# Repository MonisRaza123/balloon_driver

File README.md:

# balloon_driver
LED Balloon Targets is an LED based electronic version of the popular game Shooting Targets. In this game, the player has to shoot at balloon targets using the gun. The LEDs emulate the balloons and a laser gun is used to shoot them. The LED balloons are arranged in a 4 x 3 matrix.
One LED balloon is made of 4 LEDs and an LDR is embedded in the centre. So there is one LDR corresponding to each balloon. The player has to actually aim at the LDR by the laser gun to shoot the LED balloon. All LED balloons are lighted up initially. As soon as laser falls on any LDR, the LEDs of the corresponding balloon turn off. Once all the LED balloons go off, the buzzer is turned on to indicate the same.
Do you have what it takes to be a great shooter? Test your shooting skills using this game. Load the gun, press the trigger and shoot!

Let us first list down the requirements of the proposed project as follows:
- A device to sense the light coming from laser gun.
- An output device to emulate the balloon.
- An output device to indicate that the game is over.
- A microcontroller to do all the processing.
- A supply to power up the whole circuit.

Now we will try to place the above requirements in the six-box model:
1. INPUT: LDR (light-dependent resistor) to detect the change in light when laser falls on it. LDRs are arranged in a 4x3 matrix. 
1. OUTPUTS:
   1. 4 LEDs to emulate one balloon. Bal- loons are also arranged in a 4x3 matrix. 
   2. Buzzer to indicate that the game is complete i.e. all LED balloons have been shot at.
1. MICROCONTROLLER: The microcontroller used is ESP32 Wroom32.
1. POWER SUPPLY: For keeping the project portable, the power is supplied through a USB Mini B connector, which brings in a raw 5V. This voltage is not suitable to be fed directly to the ESP32. Therefore, LM1117 LDO voltage regulator that gives 3.3V output is used.
1. COMMUNICATION: A 4-pin connector, with Test, Reset, Vcc and GND signals, is provided for downloading code from the emulator. This ensures that the user doesn't have to disconnect the microcontroller from the PCB repeatedly to code it.

## Block Diagram

## Hardware Description
The hardware of our project comprises of two boards: 
1. Driver circuit board - Consisting of power supply, ESP32 microcontroller, buzzer and connectors.
2. LED Balloon board - Consisting of 4 x 3 LDR matrix and 4 x 3 LED balloon matrix and connectors. The LED Balloon board is stacked above the driver circuit. For this purpose, suitable connectors have been provided.

The working of the project involves the concept of multiplexing. So, before proceeding further one must know how multiplexing works.
- Multiplexing is a technique of driving large number of LEDs using only a few pins of the microcontroller. In multiplexing a set of LEDs are lit for a brief period of time, then the next set is lit, then another set and hence the cycle repeats. This continuous switching ON and OFF of LEDs is done at a rate such that it exceeds the persistence of vision and the human eye perceives all the LEDs to be ON simultaneously.
- The 4x3 matrix consists of 12 elements. The following circuit corresponds to one element of the matrix:
- Each LED balloon is made up of 4 LEDs which are connected in parallel as shown.
- An NPN transistor, BC547, has been used for low-side switching. It provides the necessary current sinking capabilities required to drive the LEDs.
- A PNP transistor, BC557, has been used for high-side switching. It provides the necessary current sourcing capabilities required to drive the LEDs.
- The SNS1 pin reads the voltage at that point using ADC. When laser light falls on the LDR, its resistance decreases, current through it increases and voltage at SNS1 pin decreases.
- So, if the voltage value at SNS1 pin is above a certain threshold value then ROW1 pin is made high, while COL1 pin is kept low. Hence all the 4 LEDs that make up one balloon light up.
- If the voltage value at SNS1 pin is below a certain threshold value then ROW1 pin is made low, while COL1 pin is kept low. Hence all the 4 LEDs that make up one balloon turn off.
- We deal with only one column at a time. Initially, first column is activated by keeping COL1 low, COL2 and COL3 are kept high, then SNS1, SNS2, SNS3, SNS4 pins are read for the four rows and the corresponding ROW pin is made high or low accordingly. Same procedure is repeated for second and third column too.

## Flowchart

## Circuit Design
### Driver Circuit
||
|:--:|
|*Driver board schematic*|

||
|:--:|
|*Driver board layout*|

### LED Balloon Circuit
||
|:--:|
|*Balloon board schematic*|

||
|:--:|
|*Balloon board layout*|

## Fabricated PCB
|||
|:--:|:--:|
|*Driver board(top)*|*Driver board(bottom)*|
|||
|*Balloon board(top)*|*Balloon board(bottom)*|

## 3D Enclosure
|||
|:--:|:--:|
|||

## Working Video

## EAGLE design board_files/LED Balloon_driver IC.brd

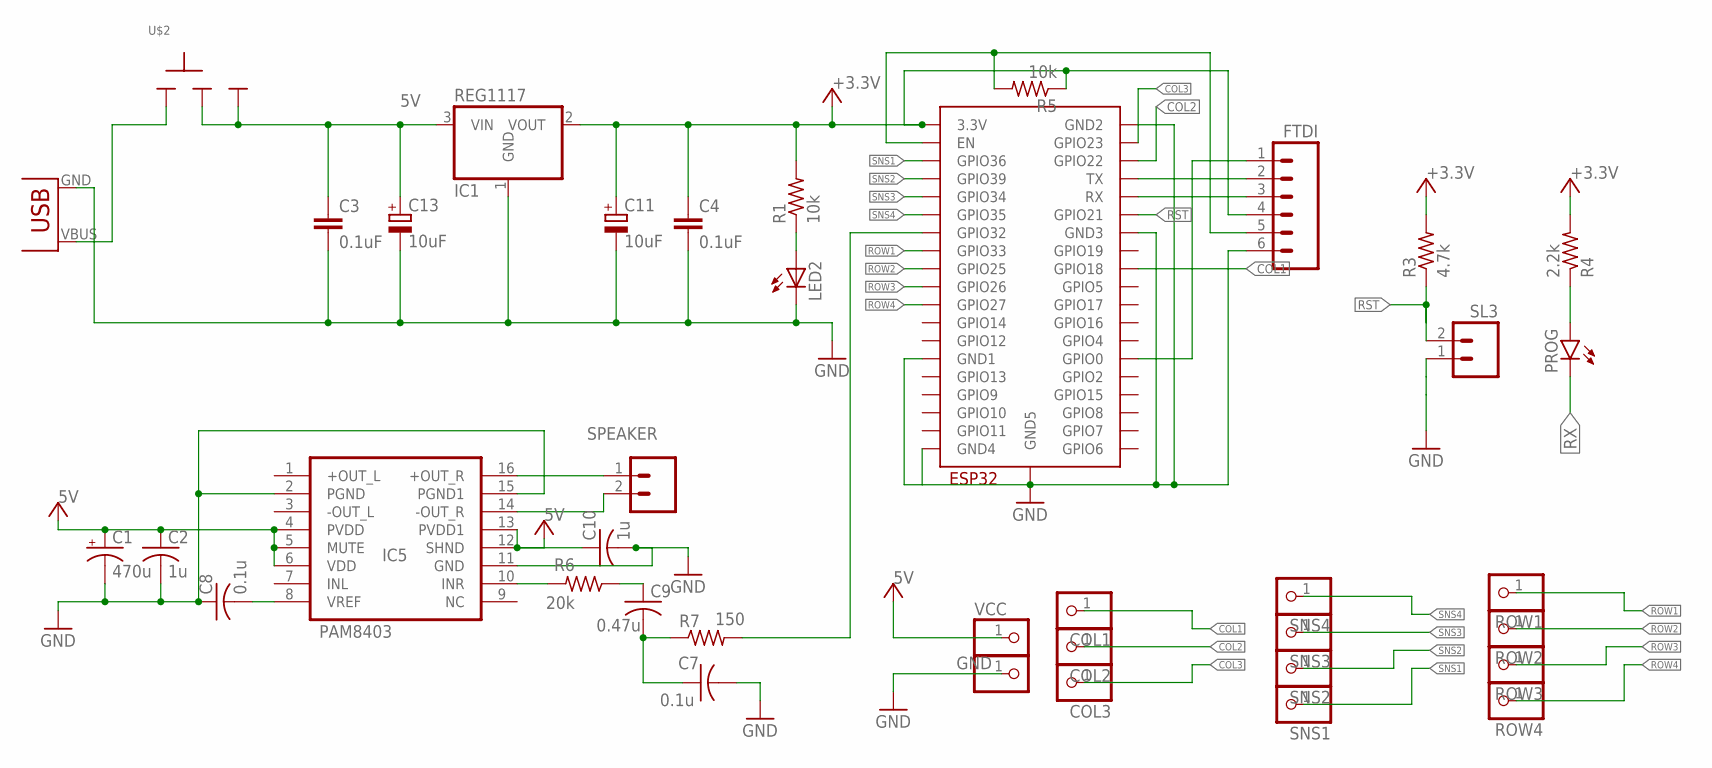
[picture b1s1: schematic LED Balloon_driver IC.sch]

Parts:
C1: 470u; E5-10,5
C2, C10: 1u; C0805
C3, C4: 0.1uF; C2.5-3
C7, C8: 0.1u; C0805
C9: 0.47u; C0805
C11, C13: 10uF; E2-5
COL1, COL2, COL3: PINHD-1X1; 1X01
ESP32_MODULE: ESP32-WROOM
GND: PINHD-1X1; 1X01
IC1: REG1117; SOT223
IC5: PAM8403; SOP-16
LED2: LED5MM
PROG: LED-RED0603; 0603-RED
R1: 10k; 0207/7
R3: 4.7k; 0207/7
R4: 2.2k; R0805
R5: 10k; R0805
R6: 20k; 0207/10
R7: 150; 0207/10
ROW1, ROW2, ROW3, ROW4: PINHD-1X1; 1X01
SL1: FTDI; 06P
SL3: M02; 02P
SNS1, SNS2, SNS3, SNS4: PINHD-1X1; 1X01
SPEAKER: M02; 02P
U$1: USB(POWER)
U$2: SLIDESWITCH-BIG; BIGSWITCH
VCC: PINHD-1X1; 1X01

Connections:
5V: C1.+, C2.1, C3.1, C10.1, C13.+, IC1.3 (VIN), IC5.4 (PVDD), IC5.5 (MUTE), IC5.6 (VDD), IC5.12 (SHND), IC5.13 (PVDD1), U$2.2, U$2.3, VCC.1
+3.3V: C4.1, C11.+, ESP32_MODULE.3V3 (3.3V), IC1.2 (VOUT), R1.2, R3.2, R4.2, R5.1, SL1.4
COL1: COL1.1, ESP32_MODULE.IO18 (GPIO18)
COL2: COL2.1, ESP32_MODULE.IO22 (GPIO22)
COL3: COL3.1, ESP32_MODULE.IO23 (GPIO23)
EN: ESP32_MODULE.EN, R5.2, SL1.5
GND: C1.-, C2.2, C3.2, C4.2, C7.2, C8.1, C10.2, C11.-, C13.-, ESP32_MODULE.GND1, ESP32_MODULE.GND2, ESP32_MODULE.GND3, ESP32_MODULE.GND4, ESP32_MODULE.GND5, GND.1, IC1.1 (GND), IC5.2 (PGND), IC5.11 (GND), IC5.15 (PGND1), LED2.K (C), SL1.6, SL3.1, U$1.GND
unnamed: IC5.16 (+OUT_R), SPEAKER.1
unnamed: IC5.10 (INR), R6.2
unnamed: C8.2, IC5.8 (VREF)
unnamed: PROG.A, R4.1
unnamed: C9.1, R6.1
unnamed: ESP32_MODULE.IO0 (GPIO0), SL1.1
unnamed: IC5.14 (-OUT_R), SPEAKER.2
unnamed: LED2.A, R1.1
unnamed: C7.1, C9.2, R7.1
unnamed: U$1.VBUS (VCC), U$2.1
PWM: ESP32_MODULE.IO32 (GPIO32), R7.2
ROW1: ESP32_MODULE.IO33 (GPIO33), ROW1.1
ROW2: ESP32_MODULE.IO25 (GPIO25), ROW2.1
ROW3: ESP32_MODULE.IO26 (GPIO26), ROW3.1
ROW4: ESP32_MODULE.IO27 (GPIO27), ROW4.1
RST: ESP32_MODULE.IO21 (GPIO21), R3.1, SL3.2
RX: ESP32_MODULE.RX, PROG.C, SL1.3
SNS1: ESP32_MODULE.SENSOR_VP (GPIO36), SNS1.1
SNS2: ESP32_MODULE.SENSOR_VN (GPIO39), SNS2.1
SNS3: ESP32_MODULE.IO34 (GPIO34), SNS3.1
SNS4: ESP32_MODULE.IO35 (GPIO35), SNS4.1
TX: ESP32_MODULE.TX, SL1.2

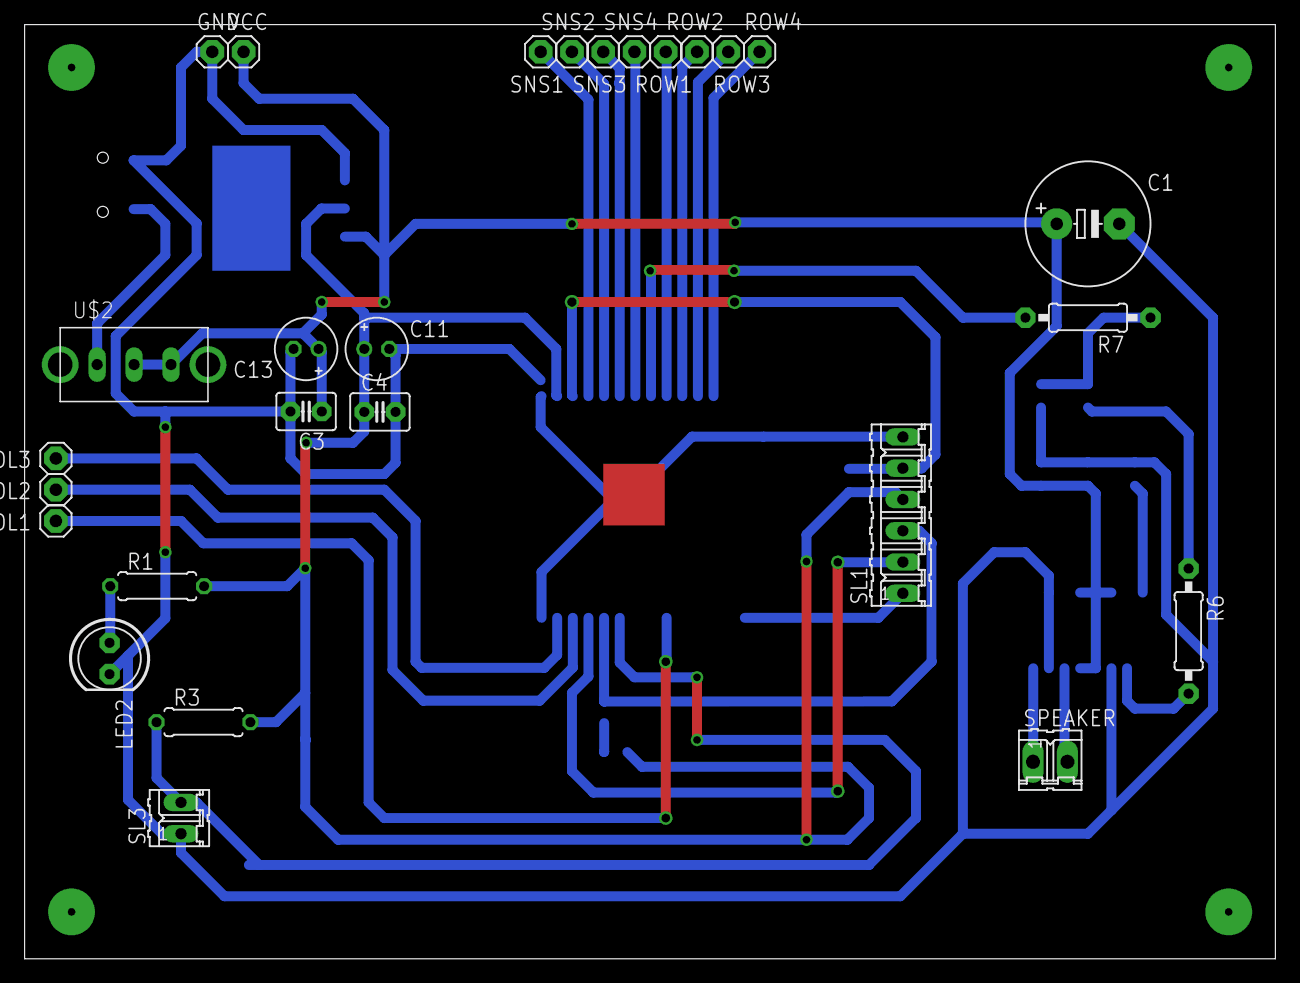
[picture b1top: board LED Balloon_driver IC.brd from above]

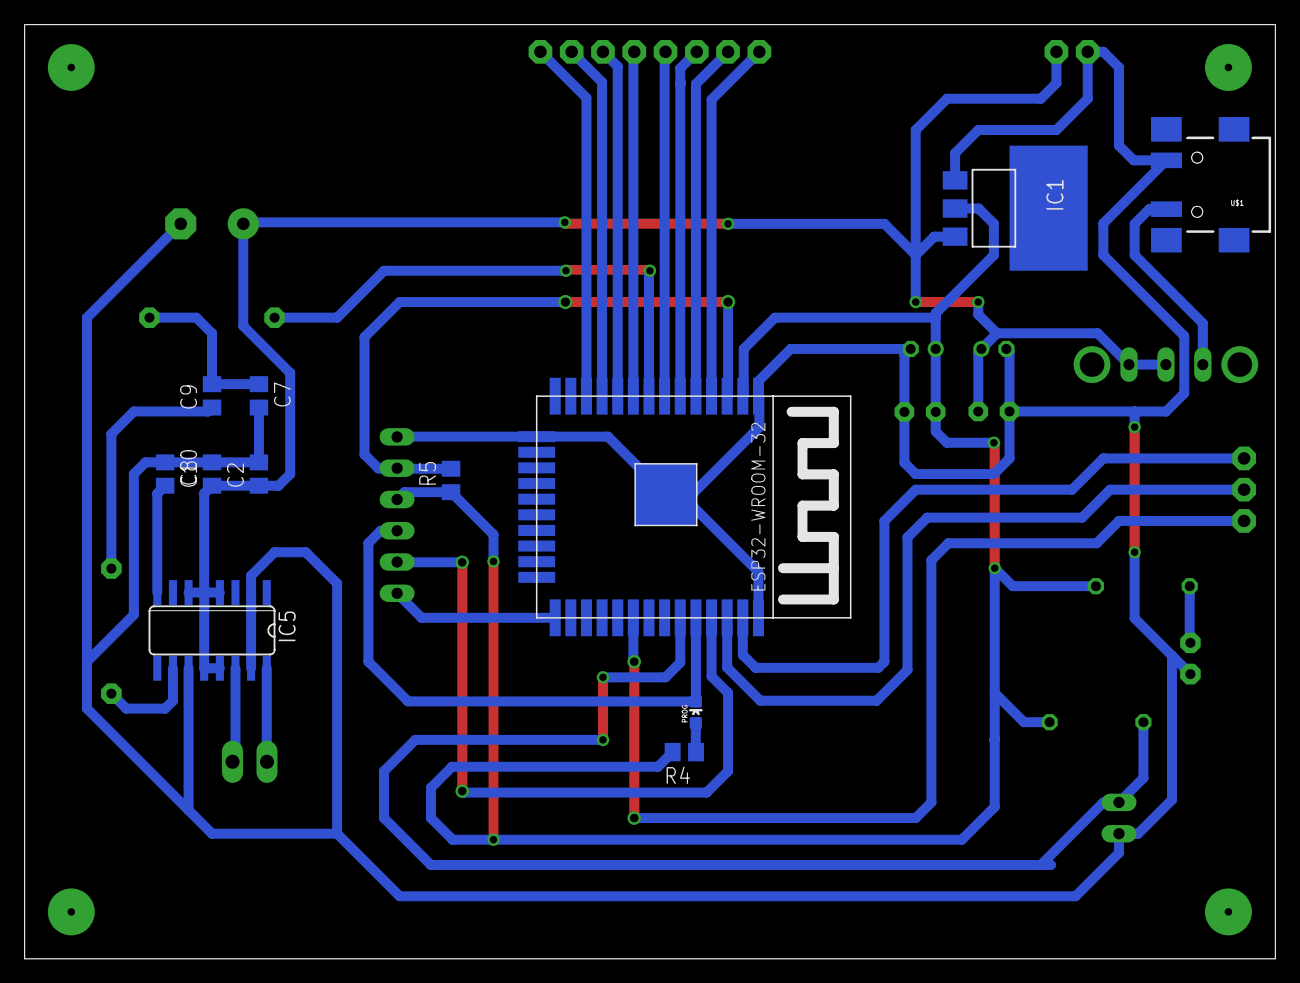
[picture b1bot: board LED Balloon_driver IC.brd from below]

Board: 2 copper layers, 101.6 x 75.9 mm, 39 parts (12 on the bottom side), 29 nets.

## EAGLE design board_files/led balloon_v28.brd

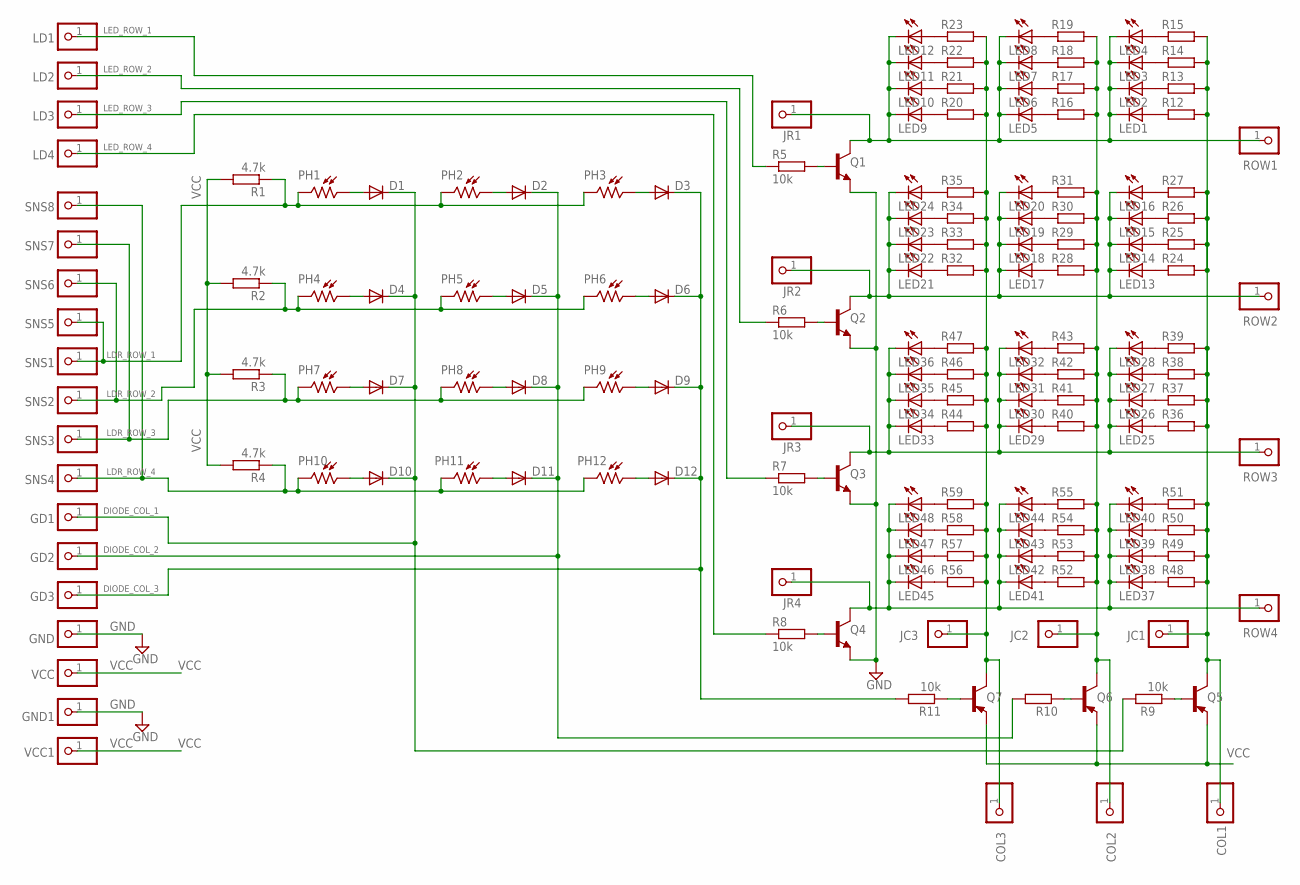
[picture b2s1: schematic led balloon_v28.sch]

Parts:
COL1, COL2, COL3: PINHD-1X1; 1X01
D1, D2, D3, D4, D5, D6, D7, D8, D9, D10, D11, D12: 1N4148DO35-7; DO35-7
GD1, GD2, GD3: PINHD-1X1; 1X01
GND, GND1: PINHD-1X1; 1X01
JC1, JC2, JC3: PINHD-1X1; 1X01
JR1, JR2, JR3, JR4: PINHD-1X1; 1X01
LD1, LD2, LD3, LD4: PINHD-1X1; 1X01
LED1, LED2, LED3, LED4, LED5, LED6, LED7, LED8, LED9, LED10, LED11, LED12, LED13, LED14, LED15, LED16, LED17, LED18, LED19, LED20, LED21, LED22, LED23, LED24, LED25, LED26, LED27, LED28, LED29, LED30, LED31, LED32, LED33, LED34, LED35, LED36, LED37, LED38, LED39, LED40, LED41, LED42, LED43, LED44, LED45, LED46, LED47, LED48: LED3MM
PH1: LDR; VT900
PH2, PH3, PH4, PH5, PH6, PH7, PH8, PH9, PH10, PH11, PH12: VT83N4; VT800
Q1, Q2, Q3, Q4: BC847ASMD; SOT23
Q5, Q6, Q7: BC807-40SMD; SOT23-BEC
R1, R2, R3, R4: 4.7k; 0204/5
R5, R6, R7, R8, R9, R10, R11: 10k; 0204/5
R12, R13, R14, R15, R16, R17, R18, R19, R20, R21, R22, R23, R24, R25, R26, R27, R28, R29, R30, R31, R32, R33, R34, R35, R36, R37, R38, R39, R40, R41, R42, R43, R44, R45, R46, R47, R48, R49, R50, R51, R52, R53, R54, R55, R56, R57, R58, R59: R-EU_R0805; R0805
ROW1, ROW2, ROW3, ROW4: PINHD-1X1; 1X01
SNS1, SNS2, SNS3, SNS4, SNS5, SNS6, SNS7, SNS8: PINHD-1X1; 1X01
VCC, VCC1: PINHD-1X1; 1X01

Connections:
DIODE_COL_1: D1.C, D4.C, D7.C, D10.C, GD1.1, R9.2
DIODE_COL_2: D2.C, D5.C, D8.C, D11.C, GD2.1, R10.2
DIODE_COL_3: D3.C, D6.C, D9.C, D12.C, GD3.1, R11.2
GND: GND.1, GND1.1, Q1.2 (E), Q2.2 (E), Q3.2 (E), Q4.2 (E)
LDR_ROW_1: PH1.2, PH2.2, PH3.2, R1.1, SNS1.1, SNS5.1
LDR_ROW_2: PH4.2, PH5.2, PH6.2, R2.1, SNS2.1, SNS6.1
LDR_ROW_3: PH7.2, PH8.2, PH9.2, R3.1, SNS3.1, SNS7.1
LDR_ROW_4: PH10.2, PH11.2, PH12.2, R4.1, SNS4.1, SNS8.1
LED_ROW_1: LD1.1, R5.1
LED_ROW_2: LD2.1, R6.1
LED_ROW_3: LD3.1, R7.1
LED_ROW_4: LD4.1, R8.1
unnamed: D1.A, PH1.1
unnamed: D2.A, PH2.1
unnamed: D3.A, PH3.1
unnamed: D6.A, PH6.1
unnamed: D5.A, PH5.1
unnamed: D4.A, PH4.1
unnamed: D7.A, PH7.1
unnamed: D8.A, PH8.1
unnamed: D9.A, PH9.1
unnamed: D12.A, PH12.1
unnamed: D11.A, PH11.1
unnamed: D10.A, PH10.1
unnamed: Q6.B, R10.1
unnamed: Q7.B, R11.1
unnamed: Q5.B, R9.1
unnamed: JR1.1, LED1.K (C), LED2.K (C), LED3.K (C), LED4.K (C), LED5.K (C), LED6.K (C), LED7.K (C), LED8.K (C), LED9.K (C), LED10.K (C), LED11.K (C), LED12.K (C), Q1.3 (C), ROW1.1
unnamed: LED1.A, R12.1
unnamed: LED2.A, R13.1
unnamed: LED3.A, R14.1
unnamed: LED4.A, R15.1
unnamed: Q1.1 (B), R5.2
unnamed: JR3.1, LED25.K (C), LED26.K (C), LED27.K (C), LED28.K (C), LED29.K (C), LED30.K (C), LED31.K (C), LED32.K (C), LED33.K (C), LED34.K (C), LED35.K (C), LED36.K (C), Q3.3 (C), ROW3.1
unnamed: LED9.A, R20.1
unnamed: LED10.A, R21.1
unnamed: LED11.A, R22.1
unnamed: COL2.1, JC2.1, Q6.C, R16.2, R17.2, R18.2, R19.2, R28.2, R29.2, R30.2, R31.2, R40.2, R41.2, R42.2, R43.2, R52.2, R53.2, R54.2, R55.2
unnamed: LED13.A, R24.1
unnamed: Q2.1 (B), R6.2
unnamed: LED5.A, R16.1
unnamed: LED6.A, R17.1
unnamed: LED7.A, R18.1
unnamed: LED8.A, R19.1
unnamed: LED14.A, R25.1
unnamed: Q3.1 (B), R7.2
unnamed: LED12.A, R23.1
unnamed: LED15.A, R26.1
unnamed: LED16.A, R27.1
unnamed: LED17.A, R28.1
unnamed: Q4.1 (B), R8.2
unnamed: LED18.A, R29.1
unnamed: LED19.A, R30.1
unnamed: LED20.A, R31.1
unnamed: COL1.1, JC1.1, Q5.C, R12.2, R13.2, R14.2, R15.2, R24.2, R25.2, R26.2, R27.2, R36.2, R37.2, R38.2, R39.2, R48.2, R49.2, R50.2, R51.2
unnamed: LED21.A, R32.1
unnamed: LED22.A, R33.1
unnamed: LED23.A, R34.1
unnamed: LED24.A, R35.1
unnamed: COL3.1, JC3.1, Q7.C, R20.2, R21.2, R22.2, R23.2, R32.2, R33.2, R34.2, R35.2, R44.2, R45.2, R46.2, R47.2, R56.2, R57.2, R58.2, R59.2
unnamed: LED25.A, R36.1
unnamed: LED26.A, R37.1
unnamed: LED27.A, R38.1
unnamed: LED28.A, R39.1
unnamed: LED29.A, R40.1
unnamed: LED30.A, R41.1
unnamed: LED31.A, R42.1
unnamed: LED32.A, R43.1
unnamed: LED33.A, R44.1
unnamed: LED34.A, R45.1
unnamed: LED35.A, R46.1
unnamed: LED36.A, R47.1
unnamed: LED37.A, R48.1
unnamed: LED38.A, R49.1
unnamed: LED39.A, R50.1
unnamed: LED40.A, R51.1
unnamed: LED41.A, R52.1
unnamed: LED42.A, R53.1
unnamed: LED43.A, R54.1
unnamed: LED44.A, R55.1
unnamed: JR2.1, LED13.K (C), LED14.K (C), LED15.K (C), LED16.K (C), LED17.K (C), LED18.K (C), LED19.K (C), LED20.K (C), LED21.K (C), LED22.K (C), LED23.K (C), LED24.K (C), Q2.3 (C), ROW2.1
unnamed: LED45.A, R56.1
unnamed: LED46.A, R57.1
unnamed: LED47.A, R58.1
unnamed: LED48.A, R59.1
unnamed: JR4.1, LED37.K (C), LED38.K (C), LED39.K (C), LED40.K (C), LED41.K (C), LED42.K (C), LED43.K (C), LED44.K (C), LED45.K (C), LED46.K (C), LED47.K (C), LED48.K (C), Q4.3 (C), ROW4.1
VCC: Q5.E, Q6.E, Q7.E, R1.2, R2.2, R3.2, R4.2, VCC.1, VCC1.1

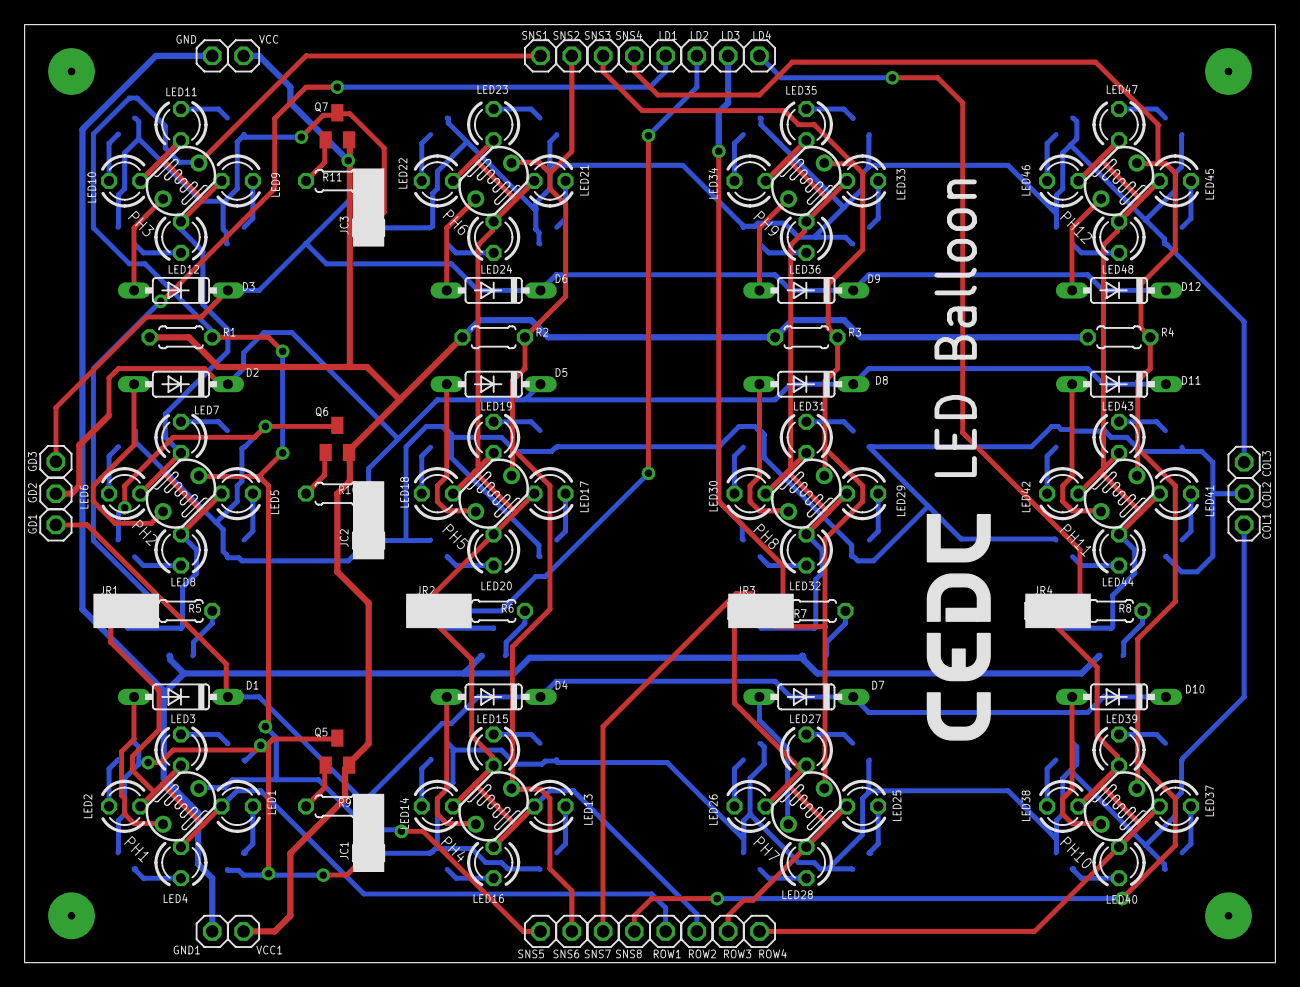
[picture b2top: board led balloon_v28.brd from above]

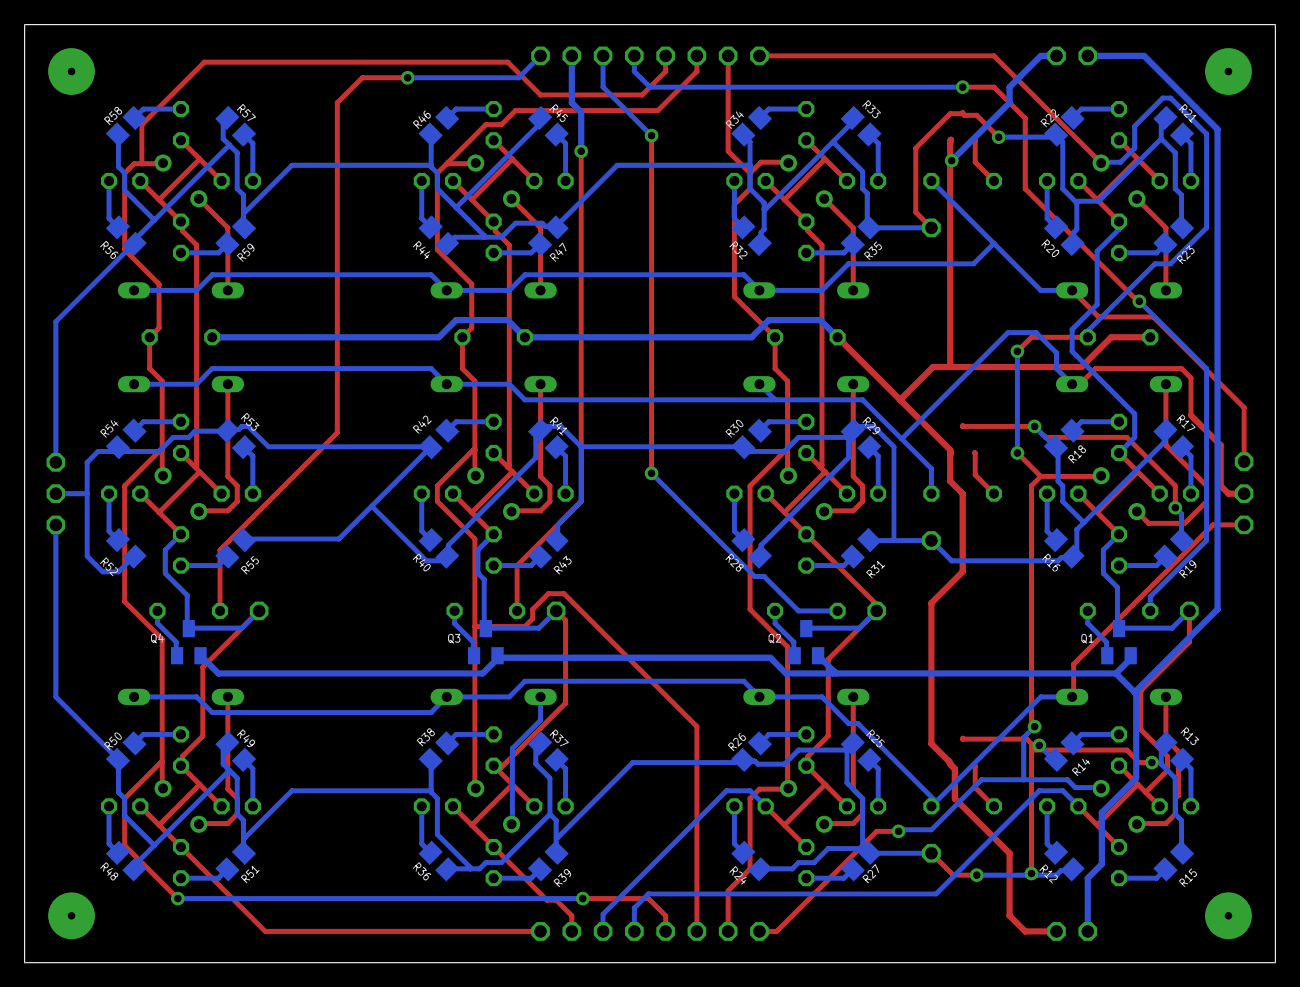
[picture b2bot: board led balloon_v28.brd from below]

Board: 2 copper layers, 101.6 x 76.2 mm, 172 parts (52 on the bottom side), 87 nets.

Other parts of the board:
E$1: LOGO-CEDT-SILK-18MM

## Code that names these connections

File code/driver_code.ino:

// Playing a digital WAV recording repeatadly using the XTronical DAC Audio library
// prints out to the serial monitor numbers counting up showing that the sound plays 
// independently of the main loop
// See www.xtronical.com for write ups on sound, the hardware required and how to make
// the wav files and include them in your code

#include "SoundData.h"
#include "XT_DAC_Audio.h"

#define SNS1 27
#define SNS2 26
#define SNS3 33
#define SNS4 32
#define LD1 35
#define LD2 34
#define LD3 39
#define LD4 36
#define GD1 23
#define GD2 22
#define GD3 18
#define THRESH 0

XT_Wav_Class* balloons[] = {new XT_Wav_Class(b1), new XT_Wav_Class(b2), new XT_Wav_Class(b3), new XT_Wav_Class(b4),
                           new XT_Wav_Class(b5), new XT_Wav_Class(b6), new XT_Wav_Class(b7), new XT_Wav_Class(b8)};

//XT_Wav_Class balloon(b1);
                                      
XT_DAC_Audio_Class DacAudio(25,3);    // Create the main player class object. 
                                      // Use GPIO 25, one of the 2 DAC pins and timer 0

int led_state[4][3];

int sensors[] = {SNS1, SNS2, SNS3, SNS4};
int leds[] = {LD1, LD2, LD3, LD4};
int grounds[] = {GD1, GD2, GD3};

//int pwm_channel = 5;
//int pwm_freq = 40000000;

void setup() {
  Serial.begin(115200);               // Not needed for sound, just to demo printing to the serial
                                      // Monitor whilst the sound plays, ensure your serial monitor
                                      // speed is set to this speed also.
//  ledcSetup(pwm_channel, pwm_freq, 8);
//  ledcAttachPin(32, pwm_channel);

  pinMode(SNS1, INPUT);
  pinMode(SNS2, INPUT);
  pinMode(SNS3, INPUT);
  pinMode(SNS4, INPUT);
  pinMode(LD1, OUTPUT);
  pinMode(LD2, OUTPUT);
  pinMode(LD3, OUTPUT);
  pinMode(LD4, OUTPUT);
  pinMode(GD1, OUTPUT);
  pinMode(GD2, OUTPUT);
  pinMode(GD3, OUTPUT);

  for(int i=0; i<4; i++){
    for(int j=0; j<3; j++){
      led_state[i][j] = HIGH;
    }
  }
}

int sound_counter = 0;
bool play = false;

void loop() {
  DacAudio.FillBuffer();                // Fill the sound buffer with data
  if(play){
    DacAudio.Play(balloons[sound_counter]);
    play = false;
  }
  
  for(int j=0; j<3; j++){
    digitalWrite(grounds[j], LOW);
    digitalWrite(grounds[(j+1)%3], HIGH);
    digitalWrite(grounds[(j+2)%3], HIGH);
    for(int i=0; i<4; i++){
      digitalWrite(leds[i], led_state[i][j]);
      delay(1);
      digitalWrite(leds[i], LOW);

      if(analogRead(sensors[i]) < THRESH && led_state[i][j] == HIGH){

        sound_counter = (sound_counter + 1)%8;
        
        led_state[i][j] = LOW;

        play = true;
      }

      if(i == 0 && j == 2){
        Serial.print(j);
        Serial.print(" ");
        Serial.print(i);
        Serial.print(" ");
        Serial.println(analogRead(sensors[i]));
      }
    }
  }
}

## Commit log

2023-10-06 updates images and video
2023-10-06 some modification
2023-10-06 added img
2023-10-06 resized img
